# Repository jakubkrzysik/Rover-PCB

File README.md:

# Projekt PCB dla Łazika (Rover-PCB)

Repozytorium zawiera projekt płytki drukowanej w programie **KiCad 9.0** dla autonomicznego lub zdalnie sterowanego łazika (Rover). 

Projekt składa się z **dwóch fizycznych płytek** zaprojektowanych na jednym schemacie (`Rover_PCB.kicad_sch`) i w dwóch osobnych plikach PCB (`Rover_PCB.kicad_pcb` oraz `Rover_PCB _Power.kicad_pcb`), które łączą się ze sobą za pomocą złącza ATX oraz taśm FFC (Flat Flexible Cable).

---

## Główny Mikrokontroler

Sercem układu sterowania jest potężny mikrokontroler:
* **Model:** `STM32H743VITx` (obudowa LQFP-100)
* **Rdzeń:** ARM Cortex-M7 o taktowaniu do 480 MHz
* **Lokalizacja:** Lewa płytka (Main Board)

---

## Podział na Płytki

Projekt składa się z dwóch osobnych płytek drukowanych:

1. **Płytka Główna (Main Control & Driver Board - `Rover_PCB.kicad_pcb`):**
   * Zawiera mikrokontroler STM32H7,
   * Przetworniki analogowo-cyfrowe ADC `HX711` do pomiaru wagi (belek tensometrycznych),
   * Filtry i transceivery magistrali CAN (`SN65HVD230`),
   * Dwa zintegrowane sterowniki mostkowe H dla silników szczotkowych prądu stałego (`VNH5019A-E`),
   * Główne stabilizatory napięć (`AMS1117-3.3` o wydajności do 800 mA dla logiki, `LM2596S-5` o wydajności do 3 A dla linii 5V oraz `LM2596S-12` o wydajności do 3 A dla linii 12V),
   * Porty wejściowe zasilania wysokoprądowego (`XT90` 24V i 48V) oraz bezpośrednie złącza interfejsowe kontrolera (USB-C, RJ45),
   * **Układy MOSFET (low-side):** 10 kluczy MOSFET (2x IRLZ44N w obudowie TO-220 oraz 8x AO3400A w obudowie SOT-23) służących do kluczowania masy dla oświetlenia zewnętrznego, diody statusowej RGY oraz buzzera.

2. **Płytka Zasilania i Interfejsów (Power Distribution & Interface Board - `Rover_PCB _Power.kicad_pcb`):**
   * Działa jako panel dystrybucji zasilania i hub połączeń interfejsów,
   * Posiada złącza silników, serwomechanizmów, interfejsów komunikacyjnych (Magistrala CAN, UART), czujników temperatury (NTC) oraz wejścia belek tensometrycznych (Load Cells),
   * Dystrybuuje zasilanie przez złącza wysokoprądowe `XT60` i `XT30` o napięciach: 12V, 24V oraz 48V,
   * Zawiera diody LED oświetlenia zewnętrznego, wielokolorową diodę statusową RGY, buzzer oraz fizyczne porty do programowania (ST-LINK) i przycisk awaryjny (Safety Button).

### Połączenia Międzypłytkowe (Inter-board Connections)
Tablice łączą się ze sobą bezpośrednio za pomocą czterech mostków kablowych:
* **ATX (J45 na Głównej $\leftrightarrow$ J48 na Zasilania):** Złącze Molex Mini-Fit Jr 24-pin przesyłające główne szyny zasilające (3.3V, 5V, 12V, 24V, 48V, GND), wyjścia prądowe sterowników silników (`OUTA1`/`OUTB1`, `OUTA2`/`OUTB2`) oraz linie sterowania oświetleniem przednim LED (`PC6_OUT` i `PB9_OUT`).
* **FFC 30-pin (J46 na Głównej $\leftrightarrow$ J49 na Zasilania):** Przesyłanie sygnałów logicznych (sygnały PWM serw, interfejsy UART, linie CAN, sygnały pomiarowe z HX711) oraz linii sterowania tylnym oświetleniem LED, diodą statusową i buzzerem (`PB0_OUT`, `PB1_OUT`, `PB5_OUT`, `PB8_OUT`, `PC7_OUT`, `PC8_OUT`, `PC9_OUT`, `PC10_OUT`).
* **FFC 20-pin (J47 na Głównej $\leftrightarrow$ J50 na Zasilania):** Przesyłanie sygnałów z pozostałych belek tensometrycznych oraz linii pomiarowych czujników temperatury NTC.
* **FFC 6-pin (J72 na Głównej $\leftrightarrow$ J71 na Zasilania):** Przedłużenie złącza programatora ST-LINK (SWD) na płytkę zasilania, co umożliwia debugowanie i programowanie urządzenia poprzez wyprowadzone tam złącze `J37` bez konieczności rozpinania konstrukcji.

---

## Specyfikacja Złączy

Poniższa lista opisuje przeznaczenie wszystkich złączy na obu płytkach oraz sposób sterowania powiązanymi urządzeniami.

### 1. Płytka Główna (Sterowanie i Sterowniki - `Rover_PCB.kicad_pcb`)

| Złącze | Nazwa w schemacie | Typ Złącza | Przeznaczenie |
| :--- | :--- | :--- | :--- |
| **J1** | `XT90_24V_IN` | XT90 (Męskie, kątowe) | Główne wejście zasilania 24V z akumulatora (zabezpieczone bezpiecznikiem F1 - 15A). Zasila regulatory step-down (5V, 12V) oraz mostki silników VNH5019A-E. |
| **J35** | `XT90_48V_IN` | XT90 (Męskie, kątowe) | Wejście wysokiego napięcia zasilania 48V do celów dystrybucyjnych (zabezpieczone bezpiecznikiem F2 - 1A na odczepie pomiarowym). |
| **J43** | `XT90_24V_OUT` | XT90 (Męskie, kątowe) | Wyjście zasilania 24V (przelotka bezpośrednia z J1). |
| **J44** | `XT90_48V_OUT` | XT90 (Męskie, kątowe) | Wyjście zasilania 48V (przelotka bezpośrednia z J35). |
| **J19** | `RJ45` | RJ45 | Złącze interfejsu sieciowego. **Uwaga:** Piny 1 i 2 są połączone z wyjściami mostka H Brushed_Motor2 (`OUTA2`/`OUTB2`), a piny 3 i 4 z zasilaniem 5V/GND, co umożliwia sterowanie zewnętrznym silnikiem lub modułem za pomocą kabla Ethernet. |
| **J38** | `USB_C_Receptacle` | USB-C 16-pin | Port USB-C podłączony bezpośrednio do linii D+/D- mikrokontrolera (komunikacja USB 2.0). |
| **J45** | `ATX` | Molex Mini-Fit Jr 2x12 | Interfejs zasilania, mostków silnikowych oraz przedniego oświetlenia, łączący z płytką zasilania. |
| **J46** | `FFC_30` | FFC Socket 30-pin (1.0mm) | Port taśmy sygnałowej i oświetlenia tylnego/statusowego, łączący z płytką zasilania. |
| **J47** | `FFC_20` | FFC Socket 20-pin (1.0mm) | Port taśmy sygnałowej dla belek tensometrycznych i czujników NTC, łączący z płytką zasilania. |
| **J72** | `FFC_6` | FFC Socket 6-pin (1.0mm) | Port taśmy interfejsu SWD (ST-LINK), łączący z płytką zasilania. |
| **J75** | `TEST_PAD 5V` | Pad testowy (1.5mm) | Punkt testowy napięcia 5V na płytce głównej. |
| **J76** | `TEST_PAD GND` | Pad testowy (1.5mm) | Punkt testowy masy (GND) na płytce głównej. |
| **J77** | `TEST_PAD 24V` | Pad testowy (1.5mm) | Punkt testowy napięcia 24V na płytce głównej. |
| **J78** | `TEST_PAD 3.3V` | Pad testowy (1.5mm) | Punkt testowy napięcia 3.3V na płytce głównej. |
| **J79** | `TEST_PAD 12V` | Pad testowy (1.5mm) | Punkt testowy napięcia 12V na płytce głównej. |

### 2. Płytka Zasilania (Złącza Wykonawcze i Dystrybucja Zasilania - `Rover_PCB _Power.kicad_pcb`)

#### Złącza Połączeniowe z Płytką Główną:
* **J48:** ATX (Molex Mini-Fit 24-pin) - interfejs szyn zasilających i wyjść silników szczotkowych/oświetlenia przedniego
* **J49:** FFC 30-pin - główna taśma sygnałowa (sterowanie serw, UART, CAN, ADCs, oświetlenie tylne/statusowe)
* **J50:** FFC 20-pin - pomocnicza taśma sygnałowa (belki tensometryczne, sensory NTC)
* **J71:** FFC 6-pin - taśma interfejsu programowania SWD (ST-LINK)

#### Port Programatora i Debuggera:
* **J37 (`STLINK`):** Złącze kołkowe 1x05 na płytce zasilania służące do bezpośredniego podpięcia programatora SWD bez konieczności rozkręcania obudowy łazika. Sygnały: `+3.3V`, `GND`, `SWDIO`, `SWCLK`, `NRST`.

#### Sterowanie Silnikami Szczotkowymi (DC Brushed Motors):
Oba złącza silników są zasilane za pośrednictwem złącza ATX z lewej płytki, gdzie zainstalowane są dedykowane układy H-bridge **VNH5019A-E** (obsługujące prąd ciągły do 12A/szczytowo 30A).
* **J2 (`Brushed_Motor1`):** Podłączenie silnika DC 1 (Linie `/OUTA1` i `/OUTB1` ze sterownika U5).
* **J3 (`Brushed_Motor2`):** Podłączenie silnika DC 2 (Linie `/OUTA2` i `/OUTB2` ze sterownika U6).

#### Serwomechanizmy (Servo Outputs):
Złącza 3-pinowe (GND, zasilanie +5V z LM2596, sygnał PWM) służące do pozycjonowania ramion, chwytaków bądź kamer. Sterowanie odbywa się bezpośrednio za pomocą wbudowanych w STM32 układów zegarowych (Timer PWM):
* **J20 (`Servo1`):** Sterowanie PWM z pinu **`PE9`** (TIM1_CH1)
* **J21 (`Servo2`):** Sterowanie PWM z pinu **`PE11`** (TIM1_CH2)
* **J22 (`Servo3`):** Sterowanie PWM z pinu **`PE13`** (TIM1_CH3)
* **J23 (`Servo4`):** Sterowanie PWM z pinu **`PE14`** (TIM1_CH4)
* **J24 (`Servo5`):** Sterowanie PWM z pinu **`PD14`** (TIM4_CH3)
* **J25 (`Servo6`):** Sterowanie PWM z pinu **`PD15`** (TIM4_CH4)
* **J26 (`Servo7`):** Sterowanie PWM z pinu **`PA6`** (TIM3_CH1)
* **J27 (`Servo8`):** Sterowanie PWM z pinu **`PA7`** (TIM3_CH2)

#### Magistrala CAN (CAN Bus Distribution):
Na płytce zintegrowano magistralę CAN, co pozwala na łączenie urządzeń zewnętrznych (np. sterowników silników BLDC, enkoderów, sensorów). Wszystkie te złącza dzielą wspólne linie `/CANH` i `/CANL` obsługiwane przez transceivery `SN65HVD230` z lewej płytki.
Złącza są typu JST EH 4-pin (GND, CANH, CANL, zasilanie) o różnych napięciach na pinie zasilającym:
* **J11 - J15 (`CAN_S1 - CAN_S5`):** Linia zasilająca podłączona do napięcia **`+12V`**.
* **J16 - J17 (`CAN_S6 - CAN7`):** Linia zasilająca podłączona do napięcia **`+24V`**.
* **J18 (`CAN8`):** Linia zasilająca podłączona do napięcia **`+48V`** (dla najbardziej obciążonych/zewnętrznych modułów).

#### Złącza Komunikacji UART:
* **J28 (`UART1`):** Podłączone do portu UART1 mikrokontrolera (linie `/TX1` i `/RX1`, zasilanie `+5V`, `GND`).
* **J29 (`UART2`):** Podłączone do portu UART2 mikrokontrolera (linie `/TX2` i `/RX2`, zasilanie `+5V`, `GND`).

#### Czujniki Belki Tensometrycznej (Load Cells):
Układ obsługuje do 4 czujników nacisku/wagi. Każde złącze to standardowe wyprowadzenie 4-pinowe (zasilanie analogowe AVDD, różnicowe wejścia sygnałowe INA+/INA- oraz GND). Pomiary są filtrowane i cyfryzowane przez przetworniki HX711 (U9-U12) znajdujące się na lewej płytce.
* **J39 (`Load_Cell1`):** Podłączone do przetwornika `U9` (linie `/AVDD`, `/INA+`, `/INA-` przesyłane przez FFC 30-pin).
* **J40 (`Load_Cell2`):** Podłączone do przetwornika `U10` (linie `/AVDD1`, `/INA1+`, `/INA1-` przesyłane przez FFC 30-pin).
* **J41 (`Load_Cell3`):** Podłączone do przetwornika `U11` (linie `/AVDD2`, `/INA2+`, `/INA2-` przesyłane przez FFC 20-pin).
* **J42 (`Load_Cell4`):** Podłączone do przetwornika `U12` (linie `/AVDD3`, `/INA3+`, `/INA3-` przesyłane przez FFC 20-pin).

#### Czujniki Temperatury NTC:
Służą do monitorowania temperatury krytycznych elementów konstrukcji (akumulatory, silniki). Termistory NTC tworzą dzielnik napięcia (zasilanie +3.3V, wyjście na ADC i GND). Pomiar odbywa się bezpośrednio za pomocą kanałów przetwornika ADC mikrokontrolera STM32:
* **J51 (`NTC1`):** Podłączony do pinu analogowego **`PC0`** (przez FFC)
* **J52 (`NTC2`):** Podłączony do pinu analogowego **`PC1`** (przez FFC)
* **J53 (`NTC3`):** Podłączony do pinu analogowego **`PC2`** (przez FFC)
* **J54 (`NTC4`):** Podłączony do pinu analogowego **`PC3`** (przez FFC)

#### Diody Sygnalizacyjne LED (Oświetlenie / Status):
Wszystkie diody LED znajdują się na płytce zasilania. Są zasilane z napięcia +12V (oświetlenie zewnętrzne) lub +24V (dioda statusowa J10) i sterowane od strony masy (low-side) za pomocą kluczy MOSFET typu N zlokalizowanych na płytce głównej:

* **Oświetlenie Przednie (Klucze MOSFET THT - IRLZ44N w obudowie TO-220):**
  * **J8 (`LED_F_R` - Przód Prawy):** Sterowane z pinu **`PB9`** (klucz Q5, sygnał `PB9_OUT`)
  * **J9 (`LED_F_L` - Przód Lewy):** Sterowane z pinu **`PC6`** (klucz Q6, sygnał `PC6_OUT`)

* **Oświetlenie Tylne (Klucze MOSFET SMD - AO3400A w obudowie SOT-23):**
  * **J4 (`LED_R_LL` - Tylny Lewy Zewnętrzny):** Sterowane z pinu **`PB0`** (klucz Q15, sygnał `PB0_OUT`)
  * **J5 (`LED_R_LR` - Tylny Lewy Wewnętrzny):** Sterowane z pinu **`PB1`** (klucz Q14, sygnał `PB1_OUT`)
  * **J6 (`LED_R_RR` - Tylny Prawy Zewnętrzny):** Sterowane z pinu **`PB5`** (klucz Q13, sygnał `PB5_OUT`)
  * **J7 (`LED_R_RL` - Tylny Prawy Wewnętrzny):** Sterowane z pinu **`PB8`** (klucz Q12, sygnał `PB8_OUT`)

* **Sygnalizacja Systemowa (Klucze MOSFET SMD - AO3400A w obudowie SOT-23):**
  * **J10 (`LED_RGY_B` - Trójkolorowa dioda statusu RGY + Buzzer):** Złącze zasilane z napięcia +24V, sterowane z czterech pinów:
    * Pin **`PC7`** (kolor czerwony LED - klucz Q11, sygnał `PC7_OUT`)
    * Pin **`PC8`** (kolor zielony LED - klucz Q16, sygnał `PC8_OUT`)
    * Pin **`PC9`** (kolor żółty LED - klucz Q17, sygnał `PC9_OUT`)
    * Pin **`PC10`** (Buzzer - klucz Q18, sygnał `PC10_OUT`)

#### Dystrybucja Zasilania Zewnętrznego (Power Distribution Ports):
Wyjścia zasilania służą do zasilania urządzeń o dużym poborze prądu.
* **Szyna 24V:**
  * `J55`, `J56`, `J57`, `J58` (złącza XT60)
  * `J59`, `J60`, `J61`, `J62` (złącza XT30)
* **Szyna 48V:**
  * `J63`, `J64` (złącza XT60)
  * `J67`, `J68` (złącza XT30)
* **Szyna 12V** (zasilana ze stabilizatora LM2596S-12):
  * `J65`, `J66` (złącza XT60)
  * `J69`, `J70` (złącza XT30)
* **Złącza Śrubowe (Terminal Blocks):**
  Umożliwiają bezpośrednie wyprowadzenie stałego napięcia (VOUT i GND) dla mniejszych odbiorników:
  * `J30` -> 3.3V
  * `J31` -> 5.0V (ze stabilizatora LM2596S-5)
  * `J32` -> 12.0V (ze stabilizatora LM2596S-12)
  * `J33` -> 24.0V (bezpośrednio z XT90_24V_IN)
  * `J34` -> 48.0V (bezpośrednio z XT90_48V_IN)

#### Monitoring Akumulatora (Battery Measurement):
* **J73 (`BAT1`):** Podłączenie pojedynczej celi / baterii do monitorowania napięcia.
* **J74 (`BAT_TOTAL`):** Podłączenie pełnego pakietu do monitorowania sumarycznego napięcia.
* **J36 (`Safety_Button`):** Złącze pod przycisk awaryjny (np. grzybek E-STOP), podłączone do pinu **`PE15`** mikrokontrolera STM32.

---

## Parametry Fizyczne PCB i Klasy Połączeń

Obie płytki w projekcie (Płytka Główna oraz Płytka Zasilania) zostały zaprojektowane z określonym stackupem i regułami szerokości połączeń w programie KiCad.

### 1. Ułożenie Warstw (Stackup)
Płytka Główna (`Rover_PCB.kicad_pcb`) oraz Płytka Zasilania (`Rover_PCB _Power.kicad_pcb`) posiadają identyczny, profesjonalny **4-warstwowy** stackup o łącznej grubości laminatu **1.6 mm** ze standardową grubością miedzi **35 µm (1 oz)** na wszystkich warstwach miedzianych:
* **F.Cu (Top)** — Zewnętrzna górna warstwa sygnałowa/mieszana.
* **In1.Cu (Internal 1)** — Wewnętrzna warstwa sygnałowo-zasilająca.
* **In2.Cu (Internal 2)** — Wewnętrzna dedykowana warstwa zasilania (szyna power).
* **B.Cu (Bottom)** — Zewnętrzna dolna warstwa sygnałowa/mieszana.

Dielektryk między warstwami zewnętrznymi a wewnętrznymi stanowi prepreg FR4 o grubości **0.1 mm**, a rdzeń wewnętrzny (core) ma grubość **1.24 mm**.

### 2. Klasy Netów (Net Classes)
W obu projektach skonfigurowano analogiczne dedykowane klasy połączeń dopasowane do obciążalności prądowej oraz typu sygnałów:

| Klasa Połączeń | Szerokość ścieżki | Odstęp (Clearance) | Średnica przelotki | Wiercenie przelotki | Zastosowanie / Przypisane Połączenia |
| :--- | :---: | :---: | :---: | :---: | :--- |
| **`Default`** | **0.20 mm** | 0.20 mm | 0.60 mm | 0.30 mm | Sygnały logiczne mikrokontrolera, GPIO, szyna `/+3.3V` |
| **`CAN`** | **0.25 mm** | 0.20 mm | 0.60 mm | 0.30 mm | Różnicowe linie magistrali CAN (`/CANH`, `/CANL`, `/CANH_ETH`, `/CANL_ETH`) |
| **`GND`** | **0.50 mm** | 0.20 mm | 0.80 mm | 0.40 mm | Masa główna układu (`/GND`) |
| **`Power10A`** | **4.00 mm** | 0.30 mm | 1.50 mm | 0.80 mm | Główna szyna wysokoprądowa zasilania `/+48V` |
| **`Power5A`** | **2.00 mm** | 0.30 mm | 1.20 mm | 0.60 mm | Szyny zasilania `/+12V` oraz `/+24V` |
| **`Power1A`** | **0.50 mm** | 0.20 mm | 0.80 mm | 0.40 mm | Szyna zasilania logiki `/+5V` |
| **`USB_FS`** | **0.20 mm** | 0.15 mm | 0.60 mm | 0.30 mm | Sygnały różnicowe portu USB-C (`/D-`, `/D+`) |

### 3. Trasowanie i Szerokości Ścieżek na Płytkach

#### A. Płytka Główna (`Rover_PCB.kicad_pcb`)
* **Trasy wysokoprądowe:** Wytrasowane z szerokościami **4.00 mm** (linia `+48V`) oraz **2.00 mm** (linie `+12V` i `+24V`).
* **Zasilanie logiki i masa:** Wytrasowane szerokością **0.50 mm** (dystrybucja masy `/GND` oraz szyna `+5V`).
* **Sygnały CAN:** Szerokość ścieżek wynosi **0.25 mm**.
* **Sygnały domyślne:** Ścieżki sygnałowe mikrokontrolera STM32 mają szerokość **0.20 mm**.
* **Ścieżki niestandardowe (Custom/Ręczne):**
  * **0.10 mm** (5 segmentów) – użyte w linii **`/RX2`** na warstwie górnej w celu wyprowadzenia trasy z gęstego obszaru wyprowadzeń MCU.
  * **1.00 mm** (5 segmentów) – użyte lokalnie w masie `/GND` oraz w linii `Net-(J1-Pin_1)`.
  * **1.1018 mm** oraz **1.5998 mm** – lokalne przewężenia (neckdown) na linii zasilania `+24V`.

#### B. Płytka Zasilania (`Rover_PCB _Power.kicad_pcb`)
* **Trasy wysokoprądowe:** Wytrasowane z szerokościami **4.00 mm** (linia `+48V` - 25 segmentów) oraz **2.00 mm** (linie `+12V` - 64 segmenty, `+24V` - 43 segmenty, `+48V` - 6 segmentów).
* **Zasilanie logiki i masa:** Wytrasowane szerokością **0.50 mm** (dystrybucja linii `/GND` - 19 segmentów oraz szyna `+5V` - 22 segmenty).
* **Sygnały CAN:** Wytrasowane ścieżkami o szerokości **0.25 mm** (łącznie 73 segmenty dla `/CANH` i `/CANL`).
* **Sygnały domyślne:** Wytrasowane ścieżkami o szerokości **0.20 mm** (łącznie 397 segmentów).
* **Ścieżki niestandardowe i przewężenia (Custom/Ręczne):**
  * **1.6998 mm** (3 segmenty) – w liniach `+12V` oraz `+48V`.
  * **1.7018 mm** (2 segmenty) – w linii `+12V`.
  * **2.6998 mm** (2 segmenty) – w linii `+48V`.
  * *Uwaga: Główne przesyłanie wysokich prądów na Płytce Zasilania jest dodatkowo wspierane przez rozległe wylewki miedziane (zones) na warstwach zewnętrznych i wewnętrznych.*

---

## Wykaz Części (BOM) do Złożenia Płytki

Poniższa tabela zawiera kompletny wykaz wszystkich elementów niezbędnych do zmontowania płytek (Płytki Głównej oraz Płytki Zasilania).
Każdy element został powiązany z konkretnym, pasującym footprintem w programie KiCad, co gwarantuje poprawność montażu po zakupie.

| Lp. | Oznaczenia na schemacie (Ref) | Wartość/Nazwa | Obudowa / Nazwa Footprintu (KiCad) | Sugerowany Numer Części (MPN) | Opis / Uwagi | Ilość |
| :--- | :--- | :--- | :--- | :--- | :--- | :--- |
| 1 | D4, D5 | D_Zener | `DO-201 (THT, raster 12.7 mm)` | **1N5349BG** | Dioda Zenera 12V, 5W | 2 |
| 2 | D1, D2 | 1N5822 | `DO-201AD (THT, raster 15.24 mm)` | **1N5822-E3/54** | Dioda Schottky 40V, 3A (THT) | 2 |
| 3 | U2 | AMS1117-3.3 | `SOT-223-3` | **AMS1117-3.3** | Stabilizator liniowy LDO 3.3V, 1A | 1 |
| 4 | Q11, Q12, Q13, Q14, Q15, Q16, Q17, Q18 | AO3400A | `SOT-23 (SMD)` | **AO3400A** | Tranzystor N-MOSFET (30V, 5.7A, Rds=19mOhm) | 8 |
| 5 | J59, J60, J61, J62, J67, J68, J69, J70 | XT30_12V_OUT | `Amass XT30U-F (pionowe żeńskie PCB)` | **Amass XT30U-F** | Złącze wysokoprądowe XT30 żeńskie pionowe na płytkę | 8 |
| 6 | J55, J56, J57, J58, J63, J64, J65, J66 | XT60_24V_OUT | `Amass XT60-M (pionowe męskie PCB)` | **Amass XT60-M** | Złącze wysokoprądowe XT60 męskie pionowe na płytkę | 8 |
| 7 | J1, J35, J43, J44 | XT90_48V_OUT | `Amass XT90PW-M (kątowe męskie PCB)` | **Amass XT90PW-M** | Wysokoprądowe złącze XT90 męskie kątowe na płytkę | 4 |
| 8 | J38 | USB_C_Receptacle_USB2.0_16P | `USB-C 16-pin GCT USB4105 (poziome)` | **GCT USB4105-GF-A** | Gniazdo USB 2.0 typu C, 16-pin, montaż mieszany SMT+THT | 1 |
| 9 | U9, U10, U11, U12 | HX711 | `SOIC-16 (szerokość 3.9 mm, raster 1.27 mm)` | **HX711** | 24-bitowy przetwornik ADC dla belek tensometrycznych | 4 |
| 10 | Q5, Q6 | IRLZ44N | `TO-220-3 (pionowy)` | **IRLZ44NPBF** | Tranzystor N-MOSFET logic-level (55V, 47A, Rds=22mOhm) | 2 |
| 11 | J2, J3, J4, J5, J6, J7, J8, J9, J36, J73, J74 | LED_R_RL | `JST EH 2-pin vertical (raster 2.50 mm)` | **JST B2B-EH-A(LF)(SN)** | Złącze JST serii EH, 2-pinowe pionowe męskie | 11 |
| 12 | J51, J52, J53, J54 | NTC1 | `JST EH 3-pin vertical (raster 2.50 mm)` | **JST B3B-EH-A(LF)(SN)** | Złącze JST serii EH, 3-pinowe pionowe męskie | 4 |
| 13 | J11, J12, J13, J14, J15, J16, J17, J18, J28, J29, J39, J40, J41, J42 | CAN7 | `JST EH 4-pin vertical (raster 2.50 mm)` | **JST B4B-EH-A(LF)(SN)** | Złącze JST serii EH, 4-pinowe pionowe męskie | 14 |
| 14 | J10 | LED_RGY_B | `JST EH 5-pin vertical (raster 2.50 mm)` | **JST B5B-EH-A(LF)(SN)** | Złącze JST serii EH, 5-pinowe pionowe męskie | 1 |
| 15 | U4 | LM2596S-12 | `TO-263-5 (D2PAK)` | **LM2596S-12/NOPB** | Przetwornica obniżająca step-down impulsowa 12V, 3A | 1 |
| 16 | U3 | LM2596S-5 | `TO-263-5 (D2PAK)` | **LM2596S-5.0/NOPB** | Przetwornica obniżająca step-down impulsowa 5V, 3A | 1 |
| 17 | F1 | 15A | `Bezpiecznik samochodowy Mini Blade (lutowany w płytkę)` | **Littelfuse 0297015.WXNV + uchwyt Littelfuse 01530007Z** | Bezpiecznik Mini Blade 15A z uchwytem lutowanym | 1 |
| 18 | F2 | 1A | `Littelfuse 395 Series (raster 5.08 mm)` | **Littelfuse 39511000000** | Bezpiecznik miniaturowy TR5 1A, zwłoczny | 1 |
| 19 | Taśma-FFC-6 | Taśma FFC 6-pin | `Taśma FFC 6-pin (raster 1.0 mm, dł. 152 mm, typ A)` | **Molex 15167-0211 (lub zamiennik 6-pin, raster 1.0mm)** | Elastyczny przewód płaski FFC łączący gniazda J71 i J72 (linie SWD ST-Link) | 1 |
| 20 | Taśma-FFC-20 | Taśma FFC 20-pin | `Taśma FFC 20-pin (raster 1.0 mm, dł. 152 mm, typ A)` | **Molex 15167-0355 (lub zamiennik 20-pin, raster 1.0mm)** | Elastyczny przewód płaski FFC łączący gniazda J47 i J50 | 1 |
| 21 | Taśma-FFC-30 | Taśma FFC 30-pin | `Taśma FFC 30-pin (raster 1.0 mm, dł. 152 mm, typ A)` | **Molex 15167-0487 (lub zamiennik 30-pin, raster 1.0mm)** | Elastyczny przewód płaski FFC łączący gniazda J46 i J49 | 1 |
| 22 | J71, J72 | FFC | `FFC/FPC 6-pin, raster 1.00 mm (poziome)` | **Molex 200528-0060** | Gniazdo taśmy elastycznej FFC 6-pin, poziome SMT | 2 |
| 23 | J47, J50 | FFC | `FFC/FPC 20-pin, raster 1.00 mm (poziome)` | **Molex 200528-0200** | Gniazdo taśmy elastycznej FFC 20-pin, poziome SMT | 2 |
| 24 | J46, J49 | Conn_01x30_Socket | `FFC/FPC 30-pin, raster 1.00 mm (poziome)` | **Molex 200528-0300** | Gniazdo taśmy elastycznej FFC 30-pin, poziome SMT | 2 |
| 25 | J45, J48 | ATX | `Molex Mini-Fit Jr 5566-24A (2x12, raster 4.2 mm)` | **Molex 39-28-1243 (lub 39-28-8240)** | Złącze ATX 24-pin pionowe męskie | 2 |
| 26 | L1, L2 | 30u | `MS42 (SMD, Neosid Ms42)` | **Neosid MS42 30uH** | Dławik/cewka indukcyjna SMD 30µH | 2 |
| 27 | J19 | RJ45 | `RJ45 Jack Ninigi GE` | **Ninigi RJ45-GE (lub Molex 95501-2881)** | Gniazdo Ethernet RJ45 8p8c THT | 1 |
| 28 | J37 | STLINK | `PinSocket 1x05 vertical, raster 2.54 mm` | **PPTC051LFBN-RC (Sullins)** | Gniazdo kołkowe (żeńskie) 1x5, raster 2.54mm | 1 |
| 29 | SW1 | SW_Push | `Tactile Switch 6x6 mm, wys. 4.3 mm (THT)` | **PTS645TL43-2 LFS** | Przycisk monostabilny (tact switch) THT | 1 |
| 30 | C5, C6 | 2.2u | `Radialny THT (Ø4.0 mm, raster 1.50 mm)` | **Panasonic ECE-A1HN2R2UB** | Kondensator elektrolityczny bipolarny 2.2µF, 50V | 2 |
| 31 | C1, C2, C3, C4 | 220u | `Radialny THT (Ø5.0 mm, raster 2.50 mm)` | **Panasonic EEU-FR1E221** | Kondensator elektrolityczny niskoimpedancyjny 220µF, 25V | 4 |
| 32 | J30, J31, J32, J33, J34 | 48V | `Phoenix MKDS-1.5-2 (raster 5.08 mm)` | **Phoenix Contact 1715721 (MKDS 1,5/2-5,08)** | Złącze śrubowe (terminal block) 2-pin do druku | 5 |
| 33 | J20, J21, J22, J23, J24, J25, J26, J27 | Servo8 | `PinHeader 1x03 vertical, raster 2.54 mm` | **Pin Header 1x03 vertical (2.54mm pitch)** | Listwa kołkowa (goldpin) 1x3, raster 2.54mm | 8 |
| 34 | R1, R4, R5, R6, R7, R8, R9, R10, R11, R12, R13, R14, R15, R16, R22 | 10k | `SMD 0603 (1608 Metric)` | **RC0603FR-0710KL** | Rezystor SMD 0603, tolerancja 1%, wartość 10k | 15 |
| 35 | R17-Terminator1 | 120 | `SMD 0603 (1608 Metric)` | **RC0603FR-07120RL** | Rezystor SMD 0603, tolerancja 1%, wartość 120 | 1 |
| 36 | R17 | 330 | `SMD 0603 (1608 Metric)` | **RC0603FR-07330RL** | Rezystor SMD 0603, tolerancja 1%, wartość 330 | 1 |
| 37 | R19, R21 | 3.9k | `SMD 0603 (1608 Metric)` | **RC0603FR-073K9L** | Rezystor SMD 0603, tolerancja 1%, wartość 3.9k | 2 |
| 38 | R18, R20 | 47k | `SMD 0603 (1608 Metric)` | **RC0603FR-0747KL** | Rezystor SMD 0603, tolerancja 1%, wartość 47k | 2 |
| 39 | R2, R3 | 5.1k | `SMD 0603 (1608 Metric)` | **RC0603FR-075K1L** | Rezystor SMD 0603, tolerancja 1%, wartość 5.1k | 2 |
| 40 | D6 | SD36_SOD323 | `SOD-323 (SMD)` | **SD36-01FTG** | Dioda TVS jedno-kierunkowa 36V, obudowa SOD-323 | 1 |
| 41 | U7, U8 | SN65HVD230 | `SOIC-8 (szerokość 3.9 mm, raster 1.27 mm)` | **SN65HVD230D** | Transceiver CAN, zasilany napięciem 3.3V | 2 |
| 42 | U1 | STM32H743VITx | `LQFP-100 (14x14 mm, raster 0.5 mm)` | **STM32H743VIT6** | Mikrokontroler ARM Cortex-M7, 2MB Flash, 1MB RAM | 1 |
| 43 | U5, U6 | VNH5019A-E | `MultiPowerSO-30 (STMicroelectronics)` | **VNH5019ATR-E** | Mostek H - sterownik silników DC szczotkowych (30A/41V) | 2 |
| 44 | D3 | LED | `LED 5.0 mm (THT)` | **WP7113ID** | Dioda LED czerwona 5mm (THT) | 1 |
| 45 | C7, C8 | 10n | `SMD 0603 (1608 Metric)` | **Yageo CC0603KRX7R9BB103** | Kondensator ceramiczny MLCC SMD 0603 X7R 10nF 50V | 2 |
| 46 | C9, C10 | 18pF | `SMD 0603 (1608 Metric)` | **CC0603JRNPO9BN180** | Kondensator ceramiczny MLCC SMD 0603 NP0 18pF 50V (dla rezonatora Y2) | 2 |
| 47 | Y2 | 8MHz | `Crystal:Crystal_SMD_3225-4Pin_3.2x2.5mm_HandSoldering` | **NX3225GD-8.000M-STD-CRA-3** | Rezonator kwarcowy SMD 3.2x2.5mm (dla STM32H7) | 1 |

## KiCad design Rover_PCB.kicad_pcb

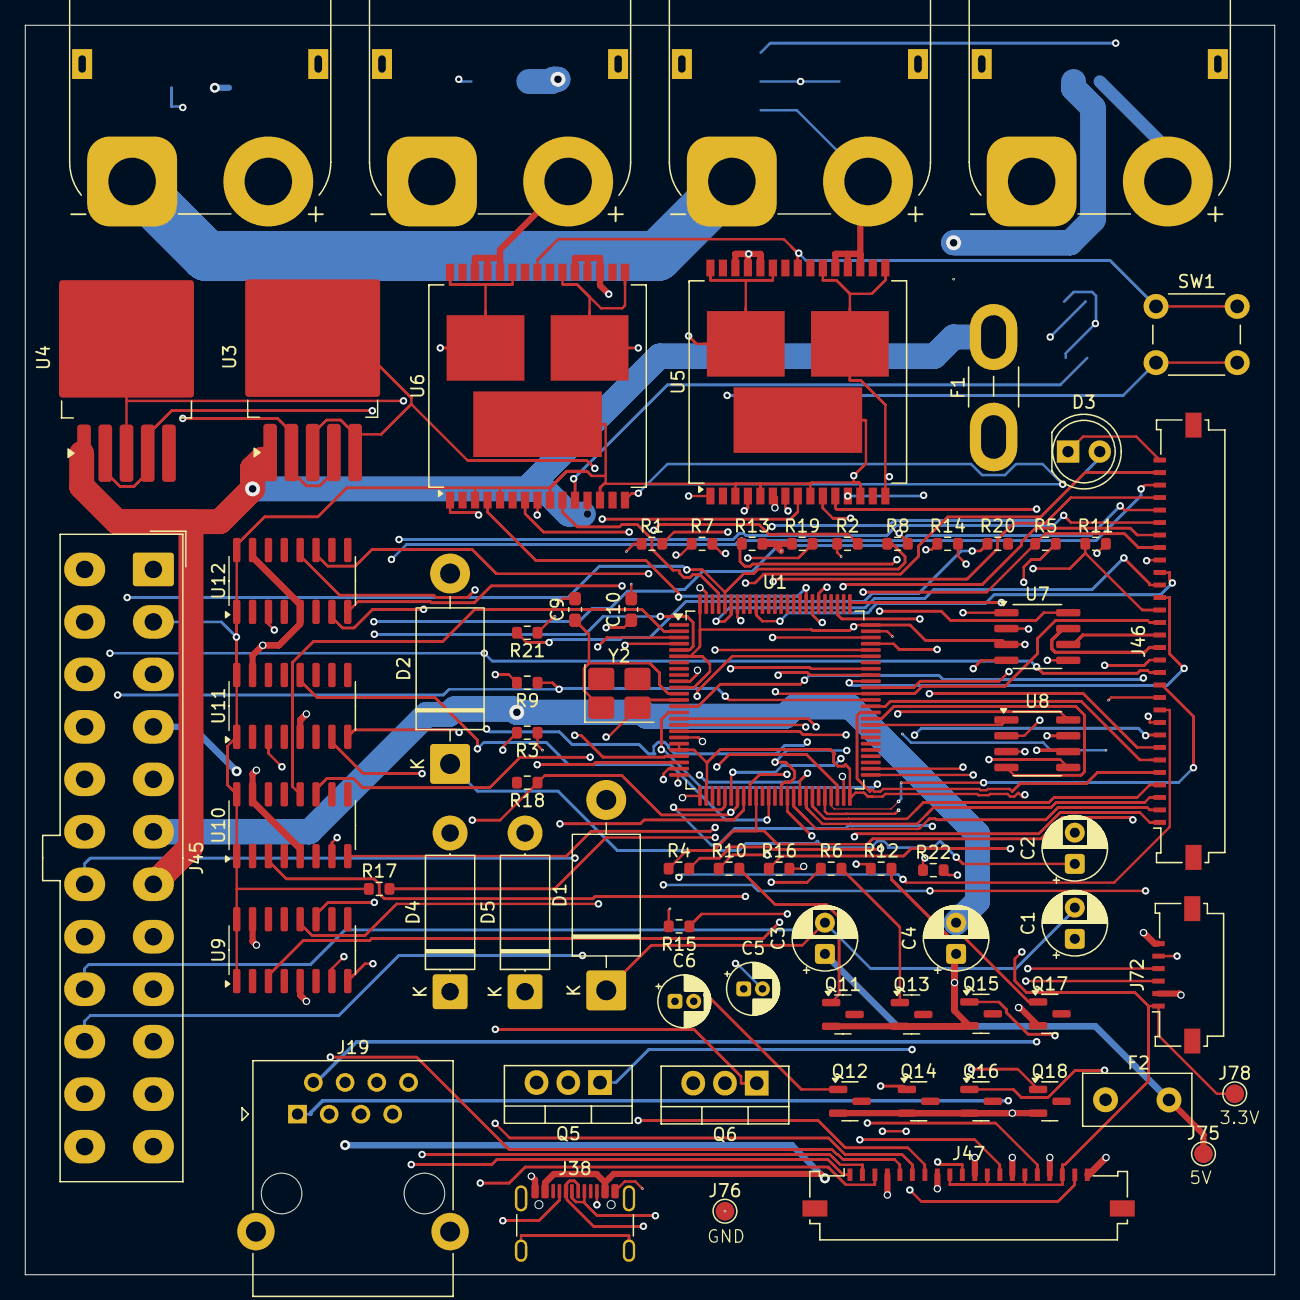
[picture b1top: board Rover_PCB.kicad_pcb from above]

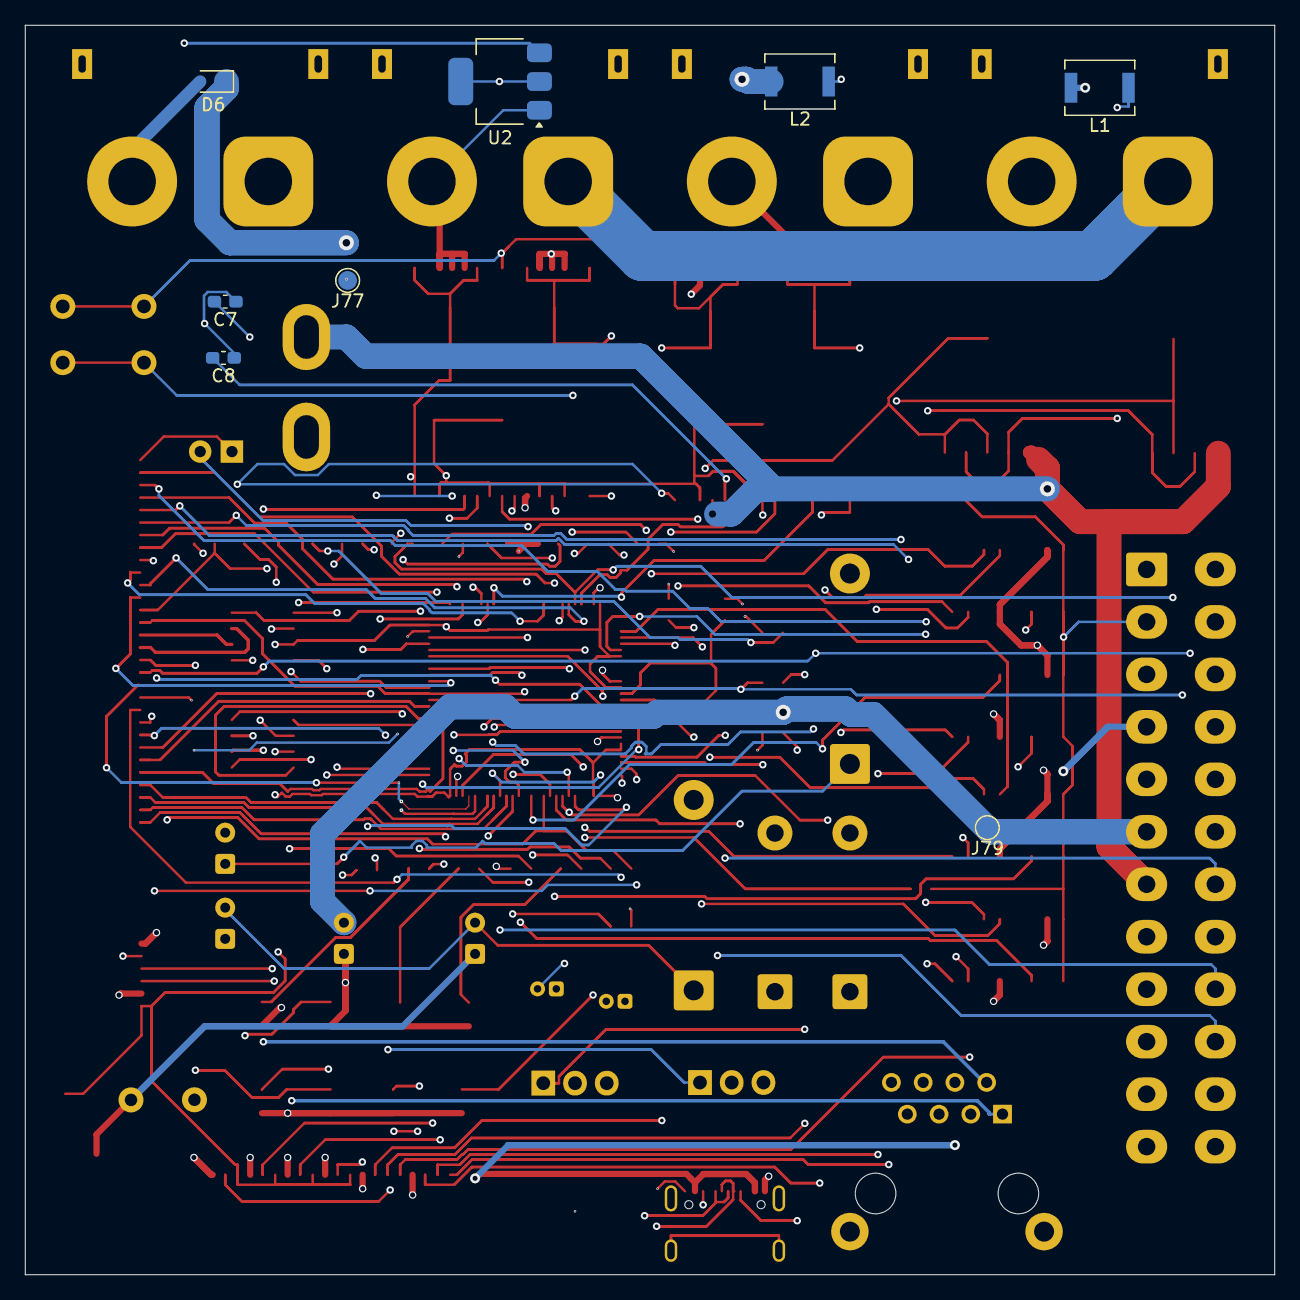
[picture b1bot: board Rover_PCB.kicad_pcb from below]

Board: 4 copper layers, 100.0 x 100.0 mm, 81 parts (8 on the bottom side), 108 nets.

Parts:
C1, C2, C3, C4: 220u; CP_Radial_D5.0mm_P2.50mm
C5, C6: 2.2u; CP_Radial_D4.0mm_P1.50mm
C7, C8: 10n; C_0603_1608Metric_Pad1.08x0.95mm_HandSolder
C9, C10: 18pF; C_0603_1608Metric_Pad1.08x0.95mm_HandSolder
D1, D2: 1N5822; D_DO-201AD_P15.24mm_Horizontal
D3: LED; LED_D5.0mm
D4, D5: D_Zener; D_5W_P12.70mm_Horizontal
D6: SD36_SOD323; D_SOD-323
F1: 15A; Fuse_Blade_Mini_directSolder
F2: 1A; Fuse_Littelfuse_395Series
J1: XT90_24V_IN; AMASS_XT90PW-M_1x02_P10.90mm_Horizontal
J19: RJ45; RJ45_Ninigi_GE
J35: XT90_48V_IN; AMASS_XT90PW-M_1x02_P10.90mm_Horizontal
J38: USB_C_Receptacle_USB2.0_16P; USB_C_Receptacle_GCT_USB4105-xx-A_16P_TopMnt_Horizontal
J43: XT90_24V_OUT; AMASS_XT90PW-M_1x02_P10.90mm_Horizontal
J44: XT90_48V_OUT; AMASS_XT90PW-M_1x02_P10.90mm_Horizontal
J45: ATX; Molex_Mini-Fit_Jr_5566-24A_2x12_P4.20mm_Vertical
J46: Conn_01x30_Socket; Molex_200528-0300_1x30-1MP_P1.00mm_Horizontal
J47: FFC; Molex_200528-0200_1x20-1MP_P1.00mm_Horizontal
J72: FFC; Molex_200528-0060_1x06-1MP_P1.00mm_Horizontal
J75: TEST_PAD 5V; TestPoint_Pad_D1.5mm
J76: TEST_PAD GND; TestPoint_Pad_D1.5mm
J77: TEST_PAD 24V; TestPoint_Pad_D1.5mm
J78: TEST_PAD 3.3V; TestPoint_Pad_D1.5mm
J79: TEST_PAD 12V; TestPoint_Pad_D1.5mm
L1, L2: 30u; L_Neosid_Ms42
Q5, Q6: IRLZ44N; TO-220-3_Vertical
Q11, Q12, Q13, Q14, Q15, Q16, Q17, Q18: AO3400A; SOT-23
R1, R4, R5, R6, R7, R8, R9, R10, R11, R12, R13, R14, R15, R16, R22: 10k; R_0603_1608Metric
R2, R3: 5.1k; R_0603_1608Metric
R17: 330; R_0603_1608Metric
R18, R20: 47k; R_0603_1608Metric
R19, R21: 3.9k; R_0603_1608Metric
SW1: SW_Push; SW_PUSH_6mm_H4.3mm
U1: STM32H743VITx; LQFP-100_14x14mm_P0.5mm
U2: AMS1117-3.3; SOT-223-3_TabPin2
U3: LM2596S-5; TO-263-5_TabPin3
U4: LM2596S-12; TO-263-5_TabPin3
U5, U6: VNH5019A-E; ST_MultiPowerSO-30
U7, U8: SN65HVD230; SOIC-8_3.9x4.9mm_P1.27mm
U9, U10, U11, U12: HX711; SOIC-16_3.9x9.9mm_P1.27mm
Y2: 8MHz; Crystal_SMD_3225-4Pin_3.2x2.5mm_HandSoldering

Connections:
/+3.3V: J45.2, J45.3, J47.9, J47.12, J47.15, J47.18, J72.1, J78.1, R17.1, SW1.1, U1.6 (VBAT), U1.11 (VDD), U1.20 (VREF+), U1.21 (VDDA), U1.27 (VDD), U1.50 (VDD), U1.75 (VDD), U1.100 (VDD), U2.2 (VO), U5.3 (VCC), U5.5 (EN/DIAGA), U5.9 (EN/DIAGB), U5.13 (VCC), U5.23 (VCC), U5.31 (VCC), U6.3 (VCC), U6.5 (EN/DIAGA), U6.9 (EN/DIAGB), U6.13 (VCC), U6.23 (VCC), U6.31 (VCC), U7.3 (VCC), U8.3 (VCC), U9.1 (VSUP), U9.16 (DVDD), U10.1 (VSUP), U10.16 (DVDD), U11.1 (VSUP), U11.16 (DVDD), U12.1 (VSUP), U12.16 (DVDD)
/+5V: C3.1, F2.2, J19.4, J38.A4 (VBUS), J38.A9 (VBUS), J38.B4 (VBUS), J38.B9 (VBUS), J45.4, J75.1, L1.2
/+12V: C4.2, J45.5, J45.6, J79.1, L2.2
/+24V: C1.1, C2.2, D6.1 (A1), F1.2, J43.1, J45.7, J45.8, J45.9, J77.1, U3.1 (VIN), U4.1 (VIN), U5.12 (VBAT), U6.12 (VBAT)
/+48V: J35.1, J44.1, J45.10, J45.11, J45.12, J45.13, J45.14
/AVDD: J46.24, U9.3 (AVDD)
/AVDD1: J46.27, U10.3 (AVDD)
/AVDD2: J47.1, U11.3 (AVDD)
/AVDD3: J47.5, U12.3 (AVDD)
/CANH: J46.15, U7.7 (CANH)
/CANH_ETH: J19.1, U8.7 (CANH)
/CANL: J46.16, U7.6 (CANL)
/CANL_ETH: J19.2, U8.6 (CANL)
/D+: J38.A6 (D+), J38.B6 (D+), U1.71 (PA12)
/D-: J38.A7 (D-), J38.B7 (D-), U1.70 (PA11)
/GND: C4.1, C5.1, C6.2, C7.1, C8.1, C9.2, C10.2, D1.2 (A), D2.2 (A), D3.1 (K), D4.2 (A), D5.2 (A), D6.2 (A2), J1.2, J19.3, J35.2, J38.A1 (GND), J38.A12 (GND), J38.B1 (GND), J38.B12 (GND), J43.2, J44.2, J45.1, J45.15, J45.16, J45.17, J45.18, J46.30, J47.4, J47.8, J47.11, J47.14, J47.17, J47.20, J72.2, J72.6, J76.1, Q5.3 (S), Q6.3 (S), Q11.2 (S), Q12.2 (S), Q13.2 (S), Q14.2 (S), Q15.2 (S), Q16.2 (S), Q17.2 (S), Q18.2 (S), R1.1, R2.1, R3.1, R13.2, R14.2, R15.2, R16.2, R19.1, R21.1, U1.10 (VSS), U1.19 (VSSA), U1.26 (VSS), U1.49 (VSS), U1.74 (VSS), U1.99 (VSS), U2.1 (GND), U5.6 (CS_DIS), U5.18 (GNDB), U5.19 (GNDB), U5.20 (GNDB), U5.26 (GNDA), U5.27 (GNDA), U5.28 (GNDA), U6.18 (GNDB), U6.19 (GNDB), U6.20 (GNDB), U6.26 (GNDA), U6.27 (GNDA), U6.28 (GNDA), U7.2 (GND), U8.2 (GND), U9.5 (AGND), U9.15 (RATE), U10.5 (AGND), U10.15 (RATE), U11.5 (AGND), U11.15 (RATE), U12.5 (AGND), U12.15 (RATE)
/INA1+: J46.29, U10.8 (INA+)
/INA1-: J46.28, U10.7 (INA-)
/INA2+: J47.3, U11.8 (INA+)
/INA2-: J47.2, U11.7 (INA-)
/INA3+: J47.7, U12.8 (INA+)
/INA3-: J47.6, U12.7 (INA-)
/INA+: J46.25, U9.8 (INA+)
/INA-: J46.26, U9.7 (INA-)
/NRST: J72.5, U1.14 (NRST)
/OUTA1: J45.22, U5.1 (OUTA), U5.25 (OUTA), U5.30 (OUTA), U5.33 (OUTA)
/OUTA2: J45.20, J46.13, U6.1 (OUTA), U6.25 (OUTA), U6.30 (OUTA), U6.33 (OUTA)
/OUTB1: J45.21, U5.15 (OUTB), U5.16 (OUTB), U5.21 (OUTB), U5.32 (OUTB)
/OUTB2: J45.19, J46.14, U6.15 (OUTB), U6.16 (OUTB), U6.21 (OUTB), U6.32 (OUTB)
/PA0: U1.22 (PA0), U5.8 (CS)
/PA1: U1.23 (PA1), U6.8 (CS)
/PA6: J46.7, U1.30 (PA6)
/PA7: J46.8, U1.31 (PA7)
/PA8: U1.67 (PA8), U5.7 (PWM)
/PA9: U1.68 (PA9), U6.7 (PWM)
/PB0: J46.23, R5.1, U1.34 (PB0)
/PB1: J46.22, R4.1, U1.35 (PB1)
/PB5: J46.21, R6.1, U1.91 (PB5)
/PB8: J46.20, R7.1, U1.95 (PB8)
/PB9: J45.24, R8.1, U1.96 (PB9)
/PB12: U1.51 (PB12), U7.4 (R)
/PB13: U1.52 (PB13), U7.1 (D)
/PC0: J47.10, U1.15 (PC0)
/PC1: J47.13, U1.16 (PC1)
/PC2: J47.16, U1.17 (PC2_C)
/PC3: J47.19, U1.18 (PC3_C)
/PC4: D4.1 (K), R18.1, R19.2, U1.32 (PC4)
/PC5: D5.1 (K), R20.1, R21.2, U1.33 (PC5)
/PC6: J45.23, R9.1, U1.63 (PC6)
/PC7: J46.17, R10.1, U1.64 (PC7)
/PC8: J46.18, R11.1, U1.65 (PC8)
/PC9: J46.19, R12.1, U1.66 (PC9)
/PC10: R22.1, U1.78 (PC10)
/PD0: U1.81 (PD0), U5.4 (INA)
/PD1: U1.82 (PD1), U5.10 (INB)
/PD2: U1.83 (PD2), U6.4 (INA)
/PD12: U1.59 (PD12), U8.1 (D)
/PD13: U1.60 (PD13), U8.4 (R)
/PD14: J46.5, U1.61 (PD14)
/PD15: J46.6, U1.62 (PD15)
/PE0: U1.97 (PE0), U6.10 (INB)
/PE3: U1.2 (PE3), U10.12 (DOUT)
/PE4: U1.3 (PE4), U10.11 (PD_SCK)
/PE5: U1.4 (PE5), U9.12 (DOUT)
/PE6: U1.5 (PE6), U9.11 (PD_SCK)
/PE7: U1.37 (PE7), U11.12 (DOUT)
/PE9: J46.1, U1.39 (PE9)
/PE10: U1.40 (PE10), U12.12 (DOUT)
/PE11: J46.2, U1.41 (PE11)
/PE12: U1.42 (PE12), U12.11 (PD_SCK)
/PE13: J46.3, U1.43 (PE13)
/PE14: J46.4, U1.44 (PE14)
/RX1: J46.10, U1.25 (PA3)
/RX2: J46.12, U1.47 (PB11)
/SWCLK: J72.4, U1.76 (PA14)
/SWDIO: J72.3, U1.72 (PA13)
/TX1: J46.9, U1.24 (PA2)
/TX2: J46.11, U1.46 (PB10)
unnamed: C5.2, U1.48 (VCAP)
unnamed: C6.1, U1.73 (VCAP)
unnamed: C1.2, C3.2, D1.1 (K), U3.3 (GND), U3.5 (~ON/OFF)
unnamed: C2.1, D2.1 (K), U4.3 (GND)
unnamed: D3.2 (A), R17.2
unnamed: F1.1, J1.1
unnamed: J38.A5 (CC1), R3.2
unnamed: J38.B5 (CC2), R2.2
unnamed: Q5.1 (G), R8.2
unnamed: Q6.1 (G), R9.2
unnamed: Q11.1 (G), R10.2
unnamed: Q12.1 (G), R7.2
unnamed: Q13.1 (G), R6.2
unnamed: Q14.1 (G), R4.2
unnamed: Q15.1 (G), R5.2
unnamed: Q16.1 (G), R11.2
unnamed: Q17.1 (G), R12.2
unnamed: Q18.1 (G), R22.2
unnamed: R1.2, SW1.2, U1.94 (BOOT0)
unnamed: C9.1, U1.12 (PH0), Y2.1
unnamed: C10.1, U1.13 (PH1), Y2.2
unnamed: F2.1, U2.3 (VI)
unnamed: L1.1, U3.2 (OUT), U3.4 (FB)
unnamed: L2.1, U4.2 (OUT), U4.4 (FB)
unnamed: C7.2, U5.11 (CP)
unnamed: C8.2, U6.11 (CP)
unnamed: R15.1, U7.8 (Rs)
unnamed: R16.1, U7.5 (Vref)
unnamed: R13.1, U8.8 (Rs)
unnamed: R14.1, U8.5 (Vref)

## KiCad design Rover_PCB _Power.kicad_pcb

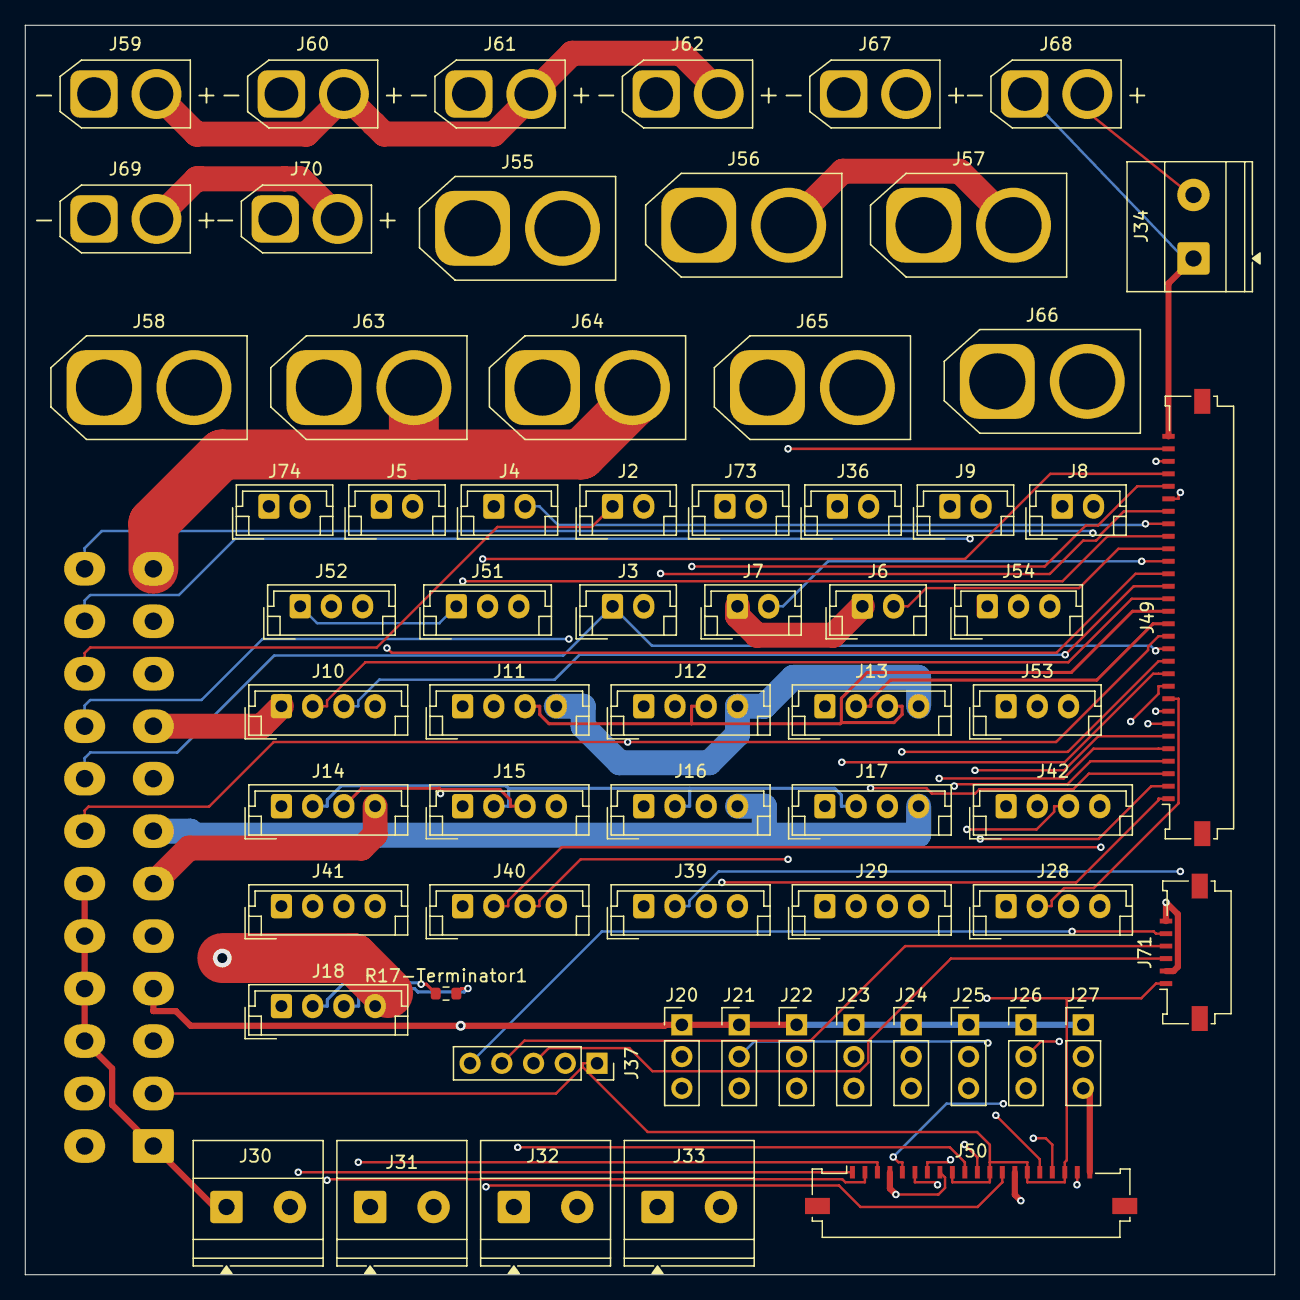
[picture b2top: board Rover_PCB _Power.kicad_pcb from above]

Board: 4 copper layers, 100.0 x 100.0 mm, 65 parts (1 on the bottom side), 52 nets.

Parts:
J2: Brushed_Motor1; JST_EH_B2B-EH-A_1x02_P2.50mm_Vertical
J3: Brushed_Motor2; JST_EH_B2B-EH-A_1x02_P2.50mm_Vertical
J4, J5: LED_R_LR; JST_EH_B2B-EH-A_1x02_P2.50mm_Vertical
J6: LED_R_RR; JST_EH_B2B-EH-A_1x02_P2.50mm_Vertical
J7: LED_R_RL; JST_EH_B2B-EH-A_1x02_P2.50mm_Vertical
J8: LED_F_R; JST_EH_B2B-EH-A_1x02_P2.50mm_Vertical
J9: LED_F_L; JST_EH_B2B-EH-A_1x02_P2.50mm_Vertical
J10: LED_U_RGY; JST_EH_B4B-EH-A_1x04_P2.50mm_Vertical
J11: CAN_S1; JST_EH_B4B-EH-A_1x04_P2.50mm_Vertical
J12: CAN_S2; JST_EH_B4B-EH-A_1x04_P2.50mm_Vertical
J13: CAN_S3; JST_EH_B4B-EH-A_1x04_P2.50mm_Vertical
J14: CAN_S4; JST_EH_B4B-EH-A_1x04_P2.50mm_Vertical
J15: CAN_S5; JST_EH_B4B-EH-A_1x04_P2.50mm_Vertical
J16: CAN_S6; JST_EH_B4B-EH-A_1x04_P2.50mm_Vertical
J17: CAN7; JST_EH_B4B-EH-A_1x04_P2.50mm_Vertical
J18: CAN8; JST_EH_B4B-EH-A_1x04_P2.50mm_Vertical
J20: Servo1; PinHeader_1x03_P2.54mm_Vertical
J21: Servo2; PinHeader_1x03_P2.54mm_Vertical
J22: Servo3; PinHeader_1x03_P2.54mm_Vertical
J23: Servo4; PinHeader_1x03_P2.54mm_Vertical
J24: Servo5; PinHeader_1x03_P2.54mm_Vertical
J25: Servo6; PinHeader_1x03_P2.54mm_Vertical
J26: Servo7; PinHeader_1x03_P2.54mm_Vertical
J27: Servo8; PinHeader_1x03_P2.54mm_Vertical
J28: UART1; JST_EH_B4B-EH-A_1x04_P2.50mm_Vertical
J29: UART2; JST_EH_B4B-EH-A_1x04_P2.50mm_Vertical
J30: 3.3V; TerminalBlock_Phoenix_MKDS-1,5-2-5.08_1x02_P5.08mm_Horizont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
J31: 5V; TerminalBlock_Phoenix_MKDS-1,5-2-5.08_1x02_P5.08mm_Horizont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
J32: 12V; TerminalBlock_Phoenix_MKDS-1,5-2-5.08_1x02_P5.08mm_Horizont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
J33: 24V; TerminalBlock_Phoenix_MKDS-1,5-2-5.08_1x02_P5.08mm_Horizont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
J34: 48V; TerminalBlock_Phoenix_MKDS-1,5-2-5.08_1x02_P5.08mm_Horizont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
J36: Safety_Button; JST_EH_B2B-EH-A_1x02_P2.50mm_Vertical
J37: STLINK; PinSocket_1x05_P2.54mm_Vertical
J39: Load_Cell1; JST_EH_B4B-EH-A_1x04_P2.50mm_Vertical
J40: Load_Cell2; JST_EH_B4B-EH-A_1x04_P2.50mm_Vertical
J41: Load_Cell3; JST_EH_B4B-EH-A_1x04_P2.50mm_Vertical
J42: Load_Cell4; JST_EH_B4B-EH-A_1x04_P2.50mm_Vertical
J48: ATX; Molex_Mini-Fit_Jr_5566-24A_2x12_P4.20mm_Vertical
J49: Conn_01x30_Socket; Molex_200528-0300_1x30-1MP_P1.00mm_Horizontal
J50: FFC; Molex_200528-0200_1x20-1MP_P1.00mm_Horizontal
J51: NTC1; JST_EH_B3B-EH-A_1x03_P2.50mm_Vertical
J52: NTC2; JST_EH_B3B-EH-A_1x03_P2.50mm_Vertical
J53: NTC3; JST_EH_B3B-EH-A_1x03_P2.50mm_Vertical
J54: NTC4; JST_EH_B3B-EH-A_1x03_P2.50mm_Vertical
J55, J56, J57, J58: XT60_24V_OUT; AMASS_XT60-M_1x02_P7.20mm_Vertical
J59, J60, J61, J62: XT30_24V_OUT; AMASS_XT30U-F_1x02_P5.0mm_Vertical
J63, J64: XT60_48V_OUT; AMASS_XT60-M_1x02_P7.20mm_Vertical
J65, J66: XT60_12V_OUT; AMASS_XT60-M_1x02_P7.20mm_Vertical
J67, J68: XT30_48V_OUT; AMASS_XT30U-F_1x02_P5.0mm_Vertical
J69, J70: XT30_12V_OUT; AMASS_XT30U-F_1x02_P5.0mm_Vertical
J71: FFC; Molex_200528-0060_1x06-1MP_P1.00mm_Horizontal
J73: BAT1; JST_EH_B2B-EH-A_1x02_P2.50mm_Vertical
J74: BAT_TOTAL; JST_EH_B2B-EH-A_1x02_P2.50mm_Vertical
R17-Terminator1: 120; R_0603_1608Metric

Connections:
/+3.3V: J30.2, J37.1, J48.2, J48.3, J50.9, J50.12, J50.15, J50.18, J51.1, J52.1, J53.1, J54.1, J71.1
/+5V: J20.1, J21.1, J22.1, J23.1, J24.1, J25.1, J26.1, J27.1, J28.4, J29.4, J31.2, J48.4
/+12V: J4.1, J5.1, J6.1, J7.1, J8.1, J9.1, J11.4, J12.4, J13.4, J14.4, J15.4, J32.2, J48.5, J48.6, J65.2, J66.2, J69.2, J70.2
/+24V: J10.1, J16.4, J17.4, J33.2, J48.7, J48.8, J48.9, J55.2, J56.2, J57.2, J58.2, J59.2, J60.2, J61.2, J62.2
/+48V: J18.4, J34.2, J48.10, J48.11, J48.12, J48.13, J48.14, J63.2, J64.2, J67.2, J68.2
/AVDD: J39.1, J49.24
/AVDD1: J40.1, J49.27
/AVDD2: J41.1, J50.1
/AVDD3: J42.1, J50.5
/CANH: J11.2, J12.2, J13.2, J14.2, J15.2, J16.2, J17.2, J18.2, J49.15, R17-Terminator1.1
/CANL: J11.3, J12.3, J13.3, J14.3, J15.3, J16.3, J17.3, J18.3, J49.16, R17-Terminator1.2
/GND: J11.1, J12.1, J13.1, J14.1, J15.1, J16.1, J17.1, J18.1, J20.3, J21.3, J22.3, J23.3, J24.3, J25.3, J26.3, J27.3, J28.1, J29.1, J30.1, J31.1, J32.1, J33.1, J34.1, J36.1, J37.2, J39.4, J40.4, J41.4, J42.4, J48.1, J48.15, J48.16, J48.17, J48.18, J49.30, J50.4, J50.8, J50.11, J50.14, J50.17, J50.20, J51.3, J52.3, J53.3, J54.3, J55.1, J56.1, J57.1, J58.1, J59.1, J60.1, J61.1, J62.1, J63.1, J64.1, J65.1, J66.1, J67.1, J68.1, J69.1, J70.1, J71.2, J71.6, J73.2, J74.2
/INA1+: J40.3, J49.29
/INA1-: J40.2, J49.28
/INA2+: J41.3, J50.3
/INA2-: J41.2, J50.2
/INA3+: J42.3, J50.7
/INA3-: J42.2, J50.6
/INA+: J39.2, J49.25
/INA-: J39.3, J49.26
/NRST: J37.5, J71.5
/OUTA1: J2.1, J48.22
/OUTA2: J3.1, J48.20, J49.13
/OUTB1: J2.2, J48.21
/OUTB2: J3.2, J48.19, J49.14
/PA6: J26.2, J49.7
/PA7: J27.2, J49.8
/PB0: J4.2, J49.23
/PB1: J5.2, J49.22
/PB5: J6.2, J49.21
/PB8: J7.2, J49.20
/PB9: J8.2, J48.24
/PC0: J50.10, J51.2
/PC1: J50.13, J52.2
/PC2: J50.16, J53.2
/PC3: J50.19, J54.2
/PC6: J9.2, J48.23
/PC7: J10.2, J49.17
/PC8: J10.3, J49.18
/PC9: J10.4, J49.19
/PD14: J24.2, J49.5
/PD15: J25.2, J49.6
/PE9: J20.2, J49.1
/PE11: J21.2, J49.2
/PE13: J22.2, J49.3
/PE14: J23.2, J49.4
/RX1: J28.3, J49.10
/RX2: J29.3, J49.12
/SWCLK: J37.4, J71.4
/SWDIO: J37.3, J71.3
/TX1: J28.2, J49.9
/TX2: J29.2, J49.11

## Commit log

2026-06-02 Projekt PCB dla Łazika (Rover-PCB) - Podział na 2 płytki (Główna i Zasilania)
2026-06-14 Aktualizacja schematu i PCB: dodanie rezonatora Y2, kondensatorow C9/C10 i punktow testowych J75-J79 oraz aktualizacja README.md i .gitignore
2026-06-14 Aktualizacja README.md: dodanie parametrow fizycznych PCB, ulozenia warstw i klas netow
2026-06-14 Usuniecie punktow testowych J75-J79 z tabeli BOM w README.md
2026-06-14 Aktualizacja plytki zasilania (Power), uaktualnienie README.md o szczegoly klas netow i grubosci sciezek na obu plytkach
